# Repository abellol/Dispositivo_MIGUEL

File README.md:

# Dispositivo_MIGUEL
Desarrollo e implementación de Robot con tecnología LiDAR
### Integrantes
El proyecto fue diseñado y desarrollado por:
| Nombre | Programa |
|:-|:-|
|Alejandro Bello León | ``Ing. Mecatrónica``|
|Ricardo Taizoo Avila Molina | ``Ing. Mecatrónica``|
|Fabio Guillermo Castellanos Lenes | ``Física``|

## Introducción
MIGUEL (Mapeo Inteligente Graficador Utilizando Escaner LiDAR) es un dispositivo autónomo diseñado para navegar por entornos controlados evitando obstaculos y tomando decisiones en tiempo real basadas en los datos que recibe. El vehículo escanea y grafica continuamente su entorno, identificando obstáculos para asegurar un movimiento eficiente dentro del espacio.

El proyecto es una propuesta que abre paso a la exploración a profuncidad de temas relacionados con la robótica, automatización y la integración de sensores.

Puedes visitar nuestra [wiki del proyecto](https://github.com/abellol/Dispositivo_MIGUEL/wiki).

## Póster

## Resultado final

https://github.com/user-attachments/assets/6533ad30-b109-4fec-b7e1-59a3a72a6980

## Vídeo explicativo del proyecto

Pueden ver el video en este [enlace](https://www.youtube.com/watch?v=PxDm3hlaaLA) a YouTube

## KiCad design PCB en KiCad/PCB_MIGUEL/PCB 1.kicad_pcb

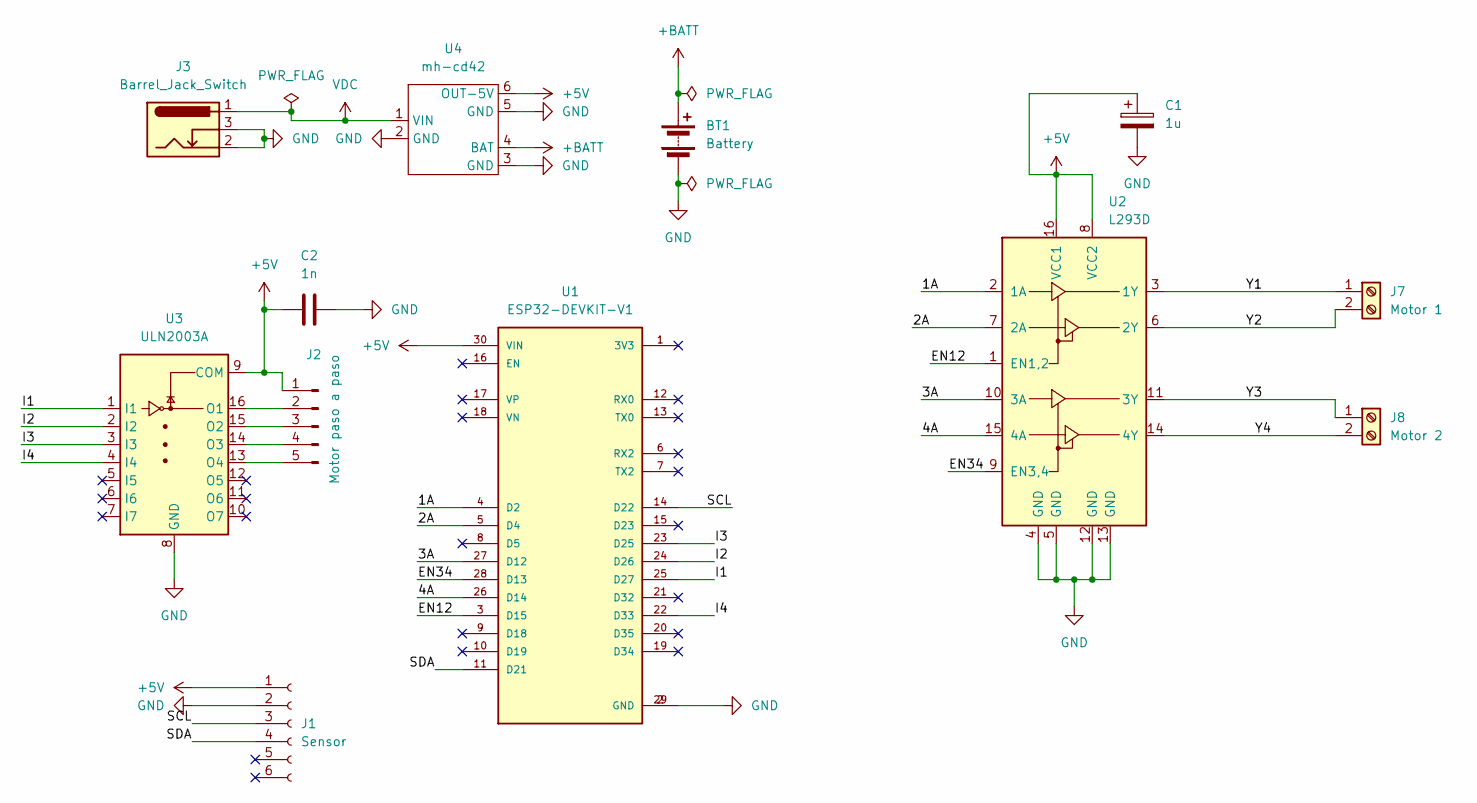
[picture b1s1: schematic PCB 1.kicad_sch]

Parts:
BT1: Battery; BatteryHolder_MPD_BH-18650-PC2
C1: 1u; CP_Radial_Tantal_D5.5mm_P5.00mm
C2: 1n; CP_Radial_D4.0mm_P2.00mm
J1: Sensor; PinSocket_1x06_P2.54mm_Vertical
J2: Motor paso a paso; PinHeader_1x05_P2.54mm_Vertical
J3: Barrel_Jack_Switch; BarrelJack_Horizontal
J7: Motor 1; TerminalBlock_bornier-2_P5.08mm
J8: Motor 2; TerminalBlock_bornier-2_P5.08mm
U1: ESP32-DEVKIT-V1; MODULE_ESP32_DEVKIT_V1; PARTREV N/A
U2: L293D; DIP-16_W7.62mm
U3: ULN2003A; DIP794W45P254L1969H508Q16
U4: mh-cd42

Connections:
+5V: C1.1, C2.1, J1.1, J2.1, U1.30 (VIN), U2.8 (VCC2), U2.16 (VCC1), U3.9 (COM), U4.6 (OUT-5V)
+BATT: BT1.1 (+), U4.4 (BAT)
/1A: U1.4 (D2), U2.2 (1A)
/2A: U1.5 (D4), U2.7 (2A)
/3A: U1.27 (D12), U2.10 (3A)
/4A: U1.26 (D14), U2.15 (4A)
/EN12: U1.3 (D15), U2.1 (EN1,2)
/EN34: U1.28 (D13), U2.9 (EN3,4)
/I1: U1.25 (D27), U3.1 (I1)
/I2: U1.24 (D26), U3.2 (I2)
/I3: U1.23 (D25), U3.3 (I3)
/I4: U1.22 (D33), U3.4 (I4)
/SCL: J1.3, U1.14 (D22)
/SDA: J1.4, U1.11 (D21)
/Y1: J7.1, U2.3 (1Y)
/Y2: J7.2, U2.6 (2Y)
/Y3: J8.1, U2.11 (3Y)
/Y4: J8.2, U2.14 (4Y)
GND: BT1.2 (-), C1.2, C2.2, J1.2, J3.2, J3.3, U1.2 (GND), U1.29 (GND), U2.4 (GND), U2.5 (GND), U2.12 (GND), U2.13 (GND), U3.8 (GND), U4.2 (GND), U4.3 (GND), U4.5 (GND)
unnamed: J2.2, U3.16 (O1)
unnamed: J2.3, U3.15 (O2)
unnamed: J2.4, U3.14 (O3)
unnamed: J2.5, U3.13 (O4)
VDC: J3.1, U4.1 (VIN)

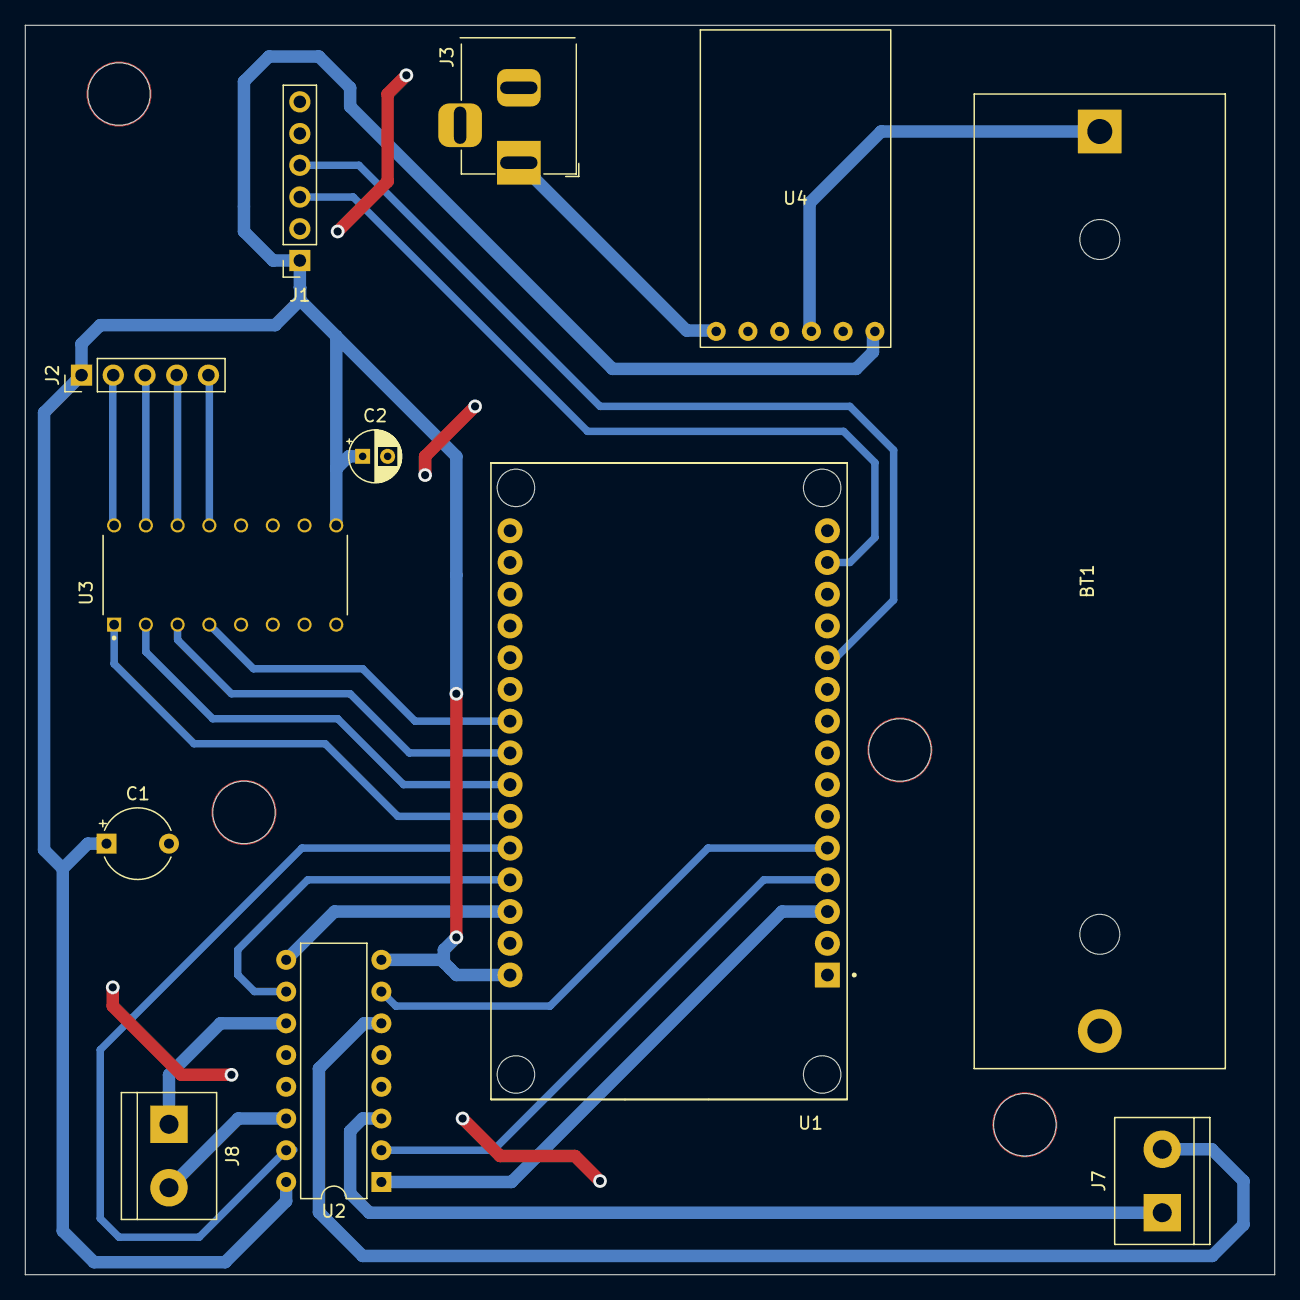
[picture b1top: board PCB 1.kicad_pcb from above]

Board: 2 copper layers, 100.0 x 100.0 mm, 12 parts (0 on the bottom side), 24 nets.

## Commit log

2024-09-15 new_libraries
2024-09-15 server at pc
2024-09-15 README
2024-09-16 Archivo para graficar en coordenadas polares
    Versión preliminar, todavía no lee datos de ninguna entrada. Pero es fácilmente configurable debido al dataframe de pandas
2024-09-16 Added functions
    Blank dataframe and update value
2024-09-17 Datos en pares
    [angle, distance]
2024-09-17 Gráfico en paralelo de datos en tiempo real
    Se crea un hilo diferente para graficar en tiempo real a medida que se van tomando datos
2024-09-17 Código graficardor final
    Gráfica en paralelo, todo funcional
2024-09-21 new_files
2024-09-21 carga de archivos
2024-09-21 Deleted files
2024-09-25 files_updated
